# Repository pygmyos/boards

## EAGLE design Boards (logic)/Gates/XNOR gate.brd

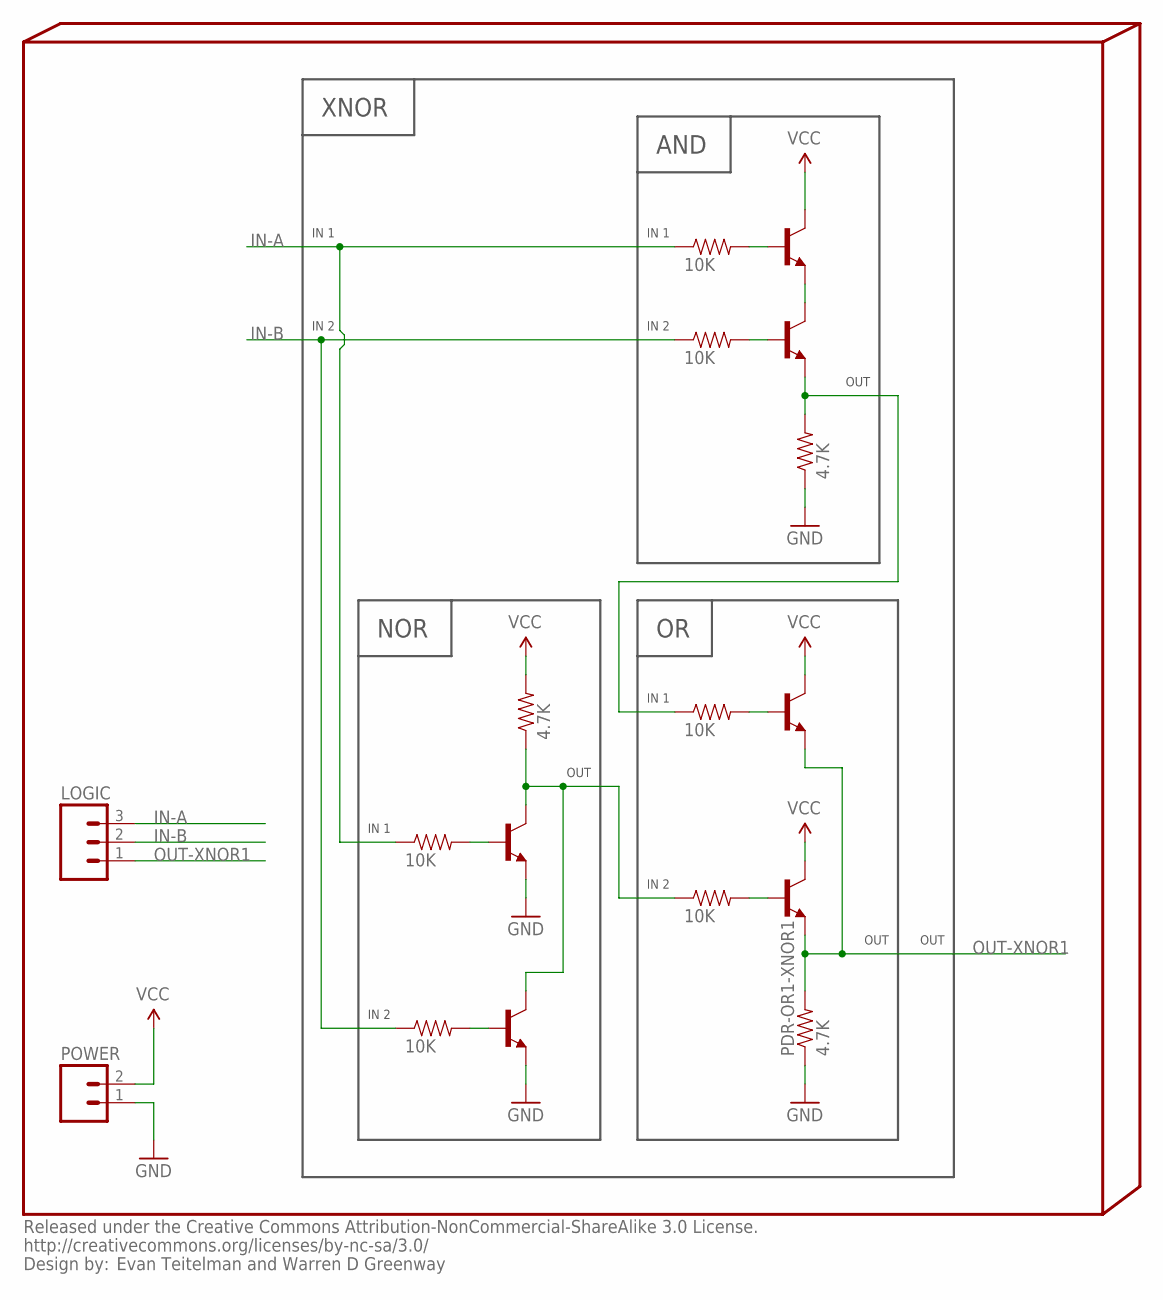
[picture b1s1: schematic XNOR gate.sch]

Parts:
INFO4: Evan Teitelman and Warren D Greenway; %CC-NC-SA
LOGIC: M03PTH; 1X03
PDR-AND1-XNOR1: 4.7K; 0402-RES
PDR-OR1-XNOR1: 4.7K; 0402-RES
POWER: M02PTH; 1X02
PUR-NOR1-XNOR1: 4.7K; 0402-RES
Q1-AND1-XNOR1, Q1-NOR1-XNOR1, Q1-OR1-XNOR1, Q2-AND1-XNOR1, Q2-NOR1-XNOR1, Q2-OR1-XNOR1: TRANSISTOR_NPNSOT23; SOT23
R1-AND1-XNOR1, R1-NOR1-XNOR1, R1-OR1-XNOR1, R2-AND1-XNOR1, R2-NOR1-XNOR1, R2-OR1-XNOR1: 10K; 0402-RES

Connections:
GND: PDR-AND1-XNOR1.1, PDR-OR1-XNOR1.1, POWER.1, Q1-NOR1-XNOR1.2 (E), Q2-NOR1-XNOR1.2 (E)
IN-A: LOGIC.3, R1-AND1-XNOR1.1, R1-NOR1-XNOR1.1
IN-B: LOGIC.2, R2-AND1-XNOR1.1, R2-NOR1-XNOR1.1
unnamed: Q1-NOR1-XNOR1.1 (B), R1-NOR1-XNOR1.2
unnamed: Q2-NOR1-XNOR1.1 (B), R2-NOR1-XNOR1.2
unnamed: Q1-AND1-XNOR1.1 (B), R1-AND1-XNOR1.2
unnamed: Q2-AND1-XNOR1.1 (B), R2-AND1-XNOR1.2
unnamed: Q2-OR1-XNOR1.1 (B), R2-OR1-XNOR1.2
unnamed: Q1-OR1-XNOR1.1 (B), R1-OR1-XNOR1.2
OUT-AND1-XNOR1: PDR-AND1-XNOR1.2, Q2-AND1-XNOR1.2 (E), R1-OR1-XNOR1.1
OUT-NOR1-XNOR1: PUR-NOR1-XNOR1.1, Q1-NOR1-XNOR1.3 (C), Q2-NOR1-XNOR1.3 (C), R2-OR1-XNOR1.1
OUT-XNOR1: LOGIC.1, PDR-OR1-XNOR1.2, Q1-OR1-XNOR1.2 (E), Q2-OR1-XNOR1.2 (E)
Q-Q-AND1-XNOR1: Q1-AND1-XNOR1.2 (E), Q2-AND1-XNOR1.3 (C)
VCC: POWER.2, PUR-NOR1-XNOR1.2, Q1-AND1-XNOR1.3 (C), Q1-OR1-XNOR1.3 (C), Q2-OR1-XNOR1.3 (C)

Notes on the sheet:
XNOR
IN 2
IN 1
OUT
AND
NOR

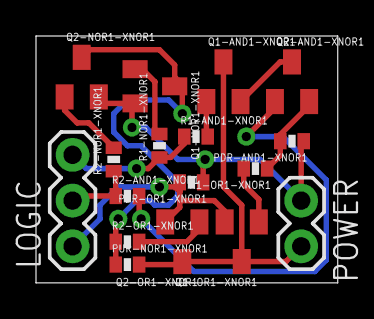
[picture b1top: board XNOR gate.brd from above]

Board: 2 copper layers, 16.8 x 13.7 mm, 18 parts (0 on the bottom side), 14 nets.

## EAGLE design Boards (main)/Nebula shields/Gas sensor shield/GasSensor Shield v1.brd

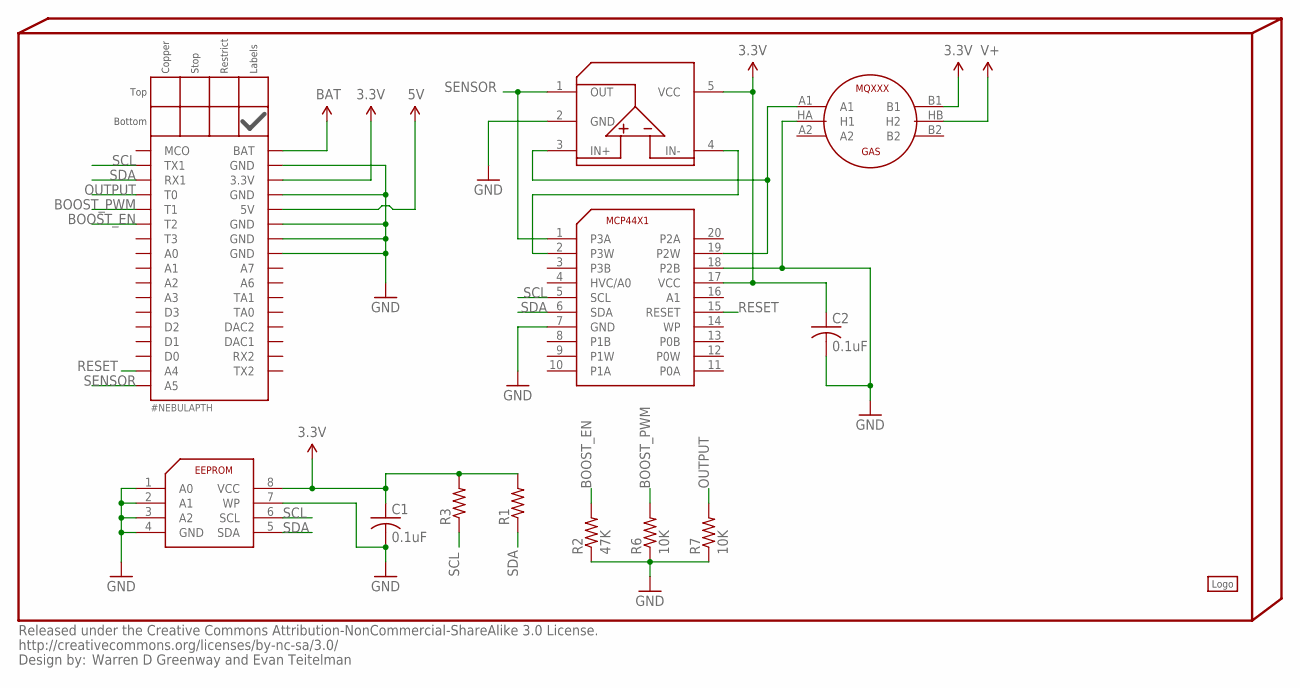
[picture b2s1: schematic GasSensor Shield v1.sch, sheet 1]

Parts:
C1, C2: 0.1uF; C0402
INFO2: Warren D Greenway and Evan Teitelman; %CC-NC-SA
LOGO1: #LOGOA-THICK
NEBULA1: #NEBULAPTH; #NEBULA-PTH
NEBULAPART1: #NEBULA-PARTLABELS-BOTTOM; #NEBULA-LABELS-BOTT
R1, R3: R-US_R0402; R0402
R2: 47K; R0402
R6, R7: 10K; R0402
U2: SENSOR-GAS-MQXXX; MQ-3
U3: EEPROM-ATMEL-AT24HC02B; TSSOP8
U4: DIGIPOT-MCP44X1; TSSOP20
U5: OPAMP-ST-LMV321RILT; SOT23-5L

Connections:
3.3V: C1.1, C2.1, NEBULA1.3.3V, R1.2, R3.2, U2.B1, U3.8 (VCC), U4.17 (VCC), U5.5 (VCC)
5V: NEBULA1.5V; also elsewhere on the board
BAT: NEBULA1.BAT; also elsewhere on the board
BOOST_EN: NEBULA1.T2, R2.2; also elsewhere on the board
BOOST_PWM: NEBULA1.T1, R6.2; also elsewhere on the board
GND: C1.2, C2.2, NEBULA1.GND1 (GND), NEBULA1.GND2 (GND), NEBULA1.GND3 (GND), NEBULA1.GND4 (GND), NEBULA1.GND5 (GND), R2.1, R6.1, R7.1, U2.HA (H1), U3.1 (A0), U3.2 (A1), U3.3 (A2), U3.4 (GND), U3.7 (WP), U4.7 (GND), U4.18 (P2B), U5.2 (GND); also elsewhere on the board
unnamed: U4.2 (P3W), U5.4 (IN-)
unnamed: U2.A1, U4.19 (P2W), U5.3 (IN+)
OUTPUT: NEBULA1.T0, R7.2; also elsewhere on the board
RESET: NEBULA1.A4, U4.15 (RESET)
SCL: NEBULA1.COM1_TX (TX1), R3.1, U3.6 (SCL), U4.5 (SCL)
SDA: NEBULA1.COM1_RX (RX1), R1.1, U3.5 (SDA), U4.6 (SDA)
SENSOR: NEBULA1.A5, U4.1 (P3A), U5.1 (OUT)
V+: U2.HB (H2); also elsewhere on the board

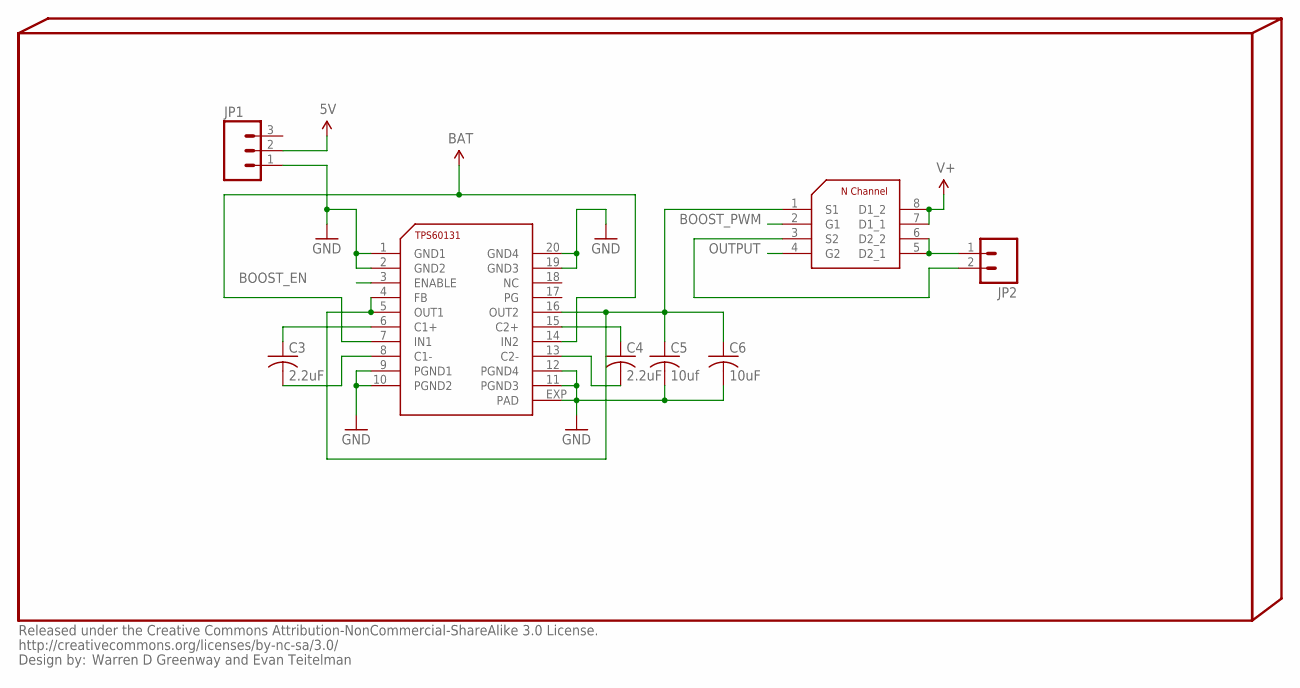
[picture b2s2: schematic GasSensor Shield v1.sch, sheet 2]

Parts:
C3, C4: 2.2uF; C0603
C5: 10uf; C0805
C6: 10uF; C0805
JP1: M03PTH; 1X03
JP2: M02PTH; 1X02
U6: REGULATOR-TI-60131; HTSSOP20PWP
U7: TRANSISTOR-VISHAY-SI7288DP; SOIC8

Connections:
5V: JP1.2; also elsewhere on the board
BAT: U6.7 (IN1), U6.14 (IN2); also elsewhere on the board
BOOST_EN: U6.3 (ENABLE); also elsewhere on the board
BOOST_PWM: U7.2 (G1); also elsewhere on the board
GND: C5.2, C6.2, JP1.1, U6.1 (GND1), U6.2 (GND2), U6.9 (PGND1), U6.10 (PGND2), U6.11 (PGND3), U6.12 (PGND4), U6.19 (GND3), U6.20 (GND4), U6.EXP (PAD); also elsewhere on the board
unnamed: C5.1, C6.1, U6.4 (FB), U6.5 (OUT1), U6.16 (OUT2), U7.1 (S1)
unnamed: C4.2, U6.13 (C2-)
unnamed: C4.1, U6.15 (C2+)
unnamed: C3.1, U6.6 (C1+)
unnamed: C3.2, U6.8 (C1-)
unnamed: JP2.1, U7.5 (D2_1), U7.6 (D2_2)
unnamed: JP2.2, U7.3 (S2)
OUTPUT: U7.4 (G2); also elsewhere on the board
V+: U7.7 (D1_1), U7.8 (D1_2); also elsewhere on the board

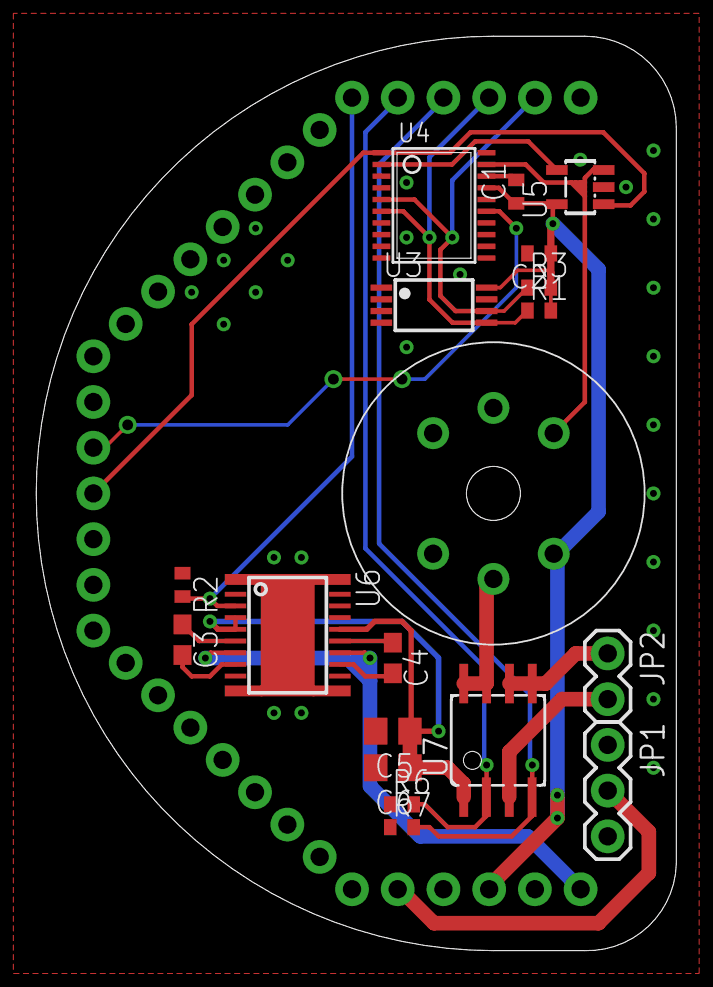
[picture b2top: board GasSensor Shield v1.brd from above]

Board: 2 copper layers, 35.6 x 50.8 mm, 23 parts (0 on the bottom side), 21 nets.

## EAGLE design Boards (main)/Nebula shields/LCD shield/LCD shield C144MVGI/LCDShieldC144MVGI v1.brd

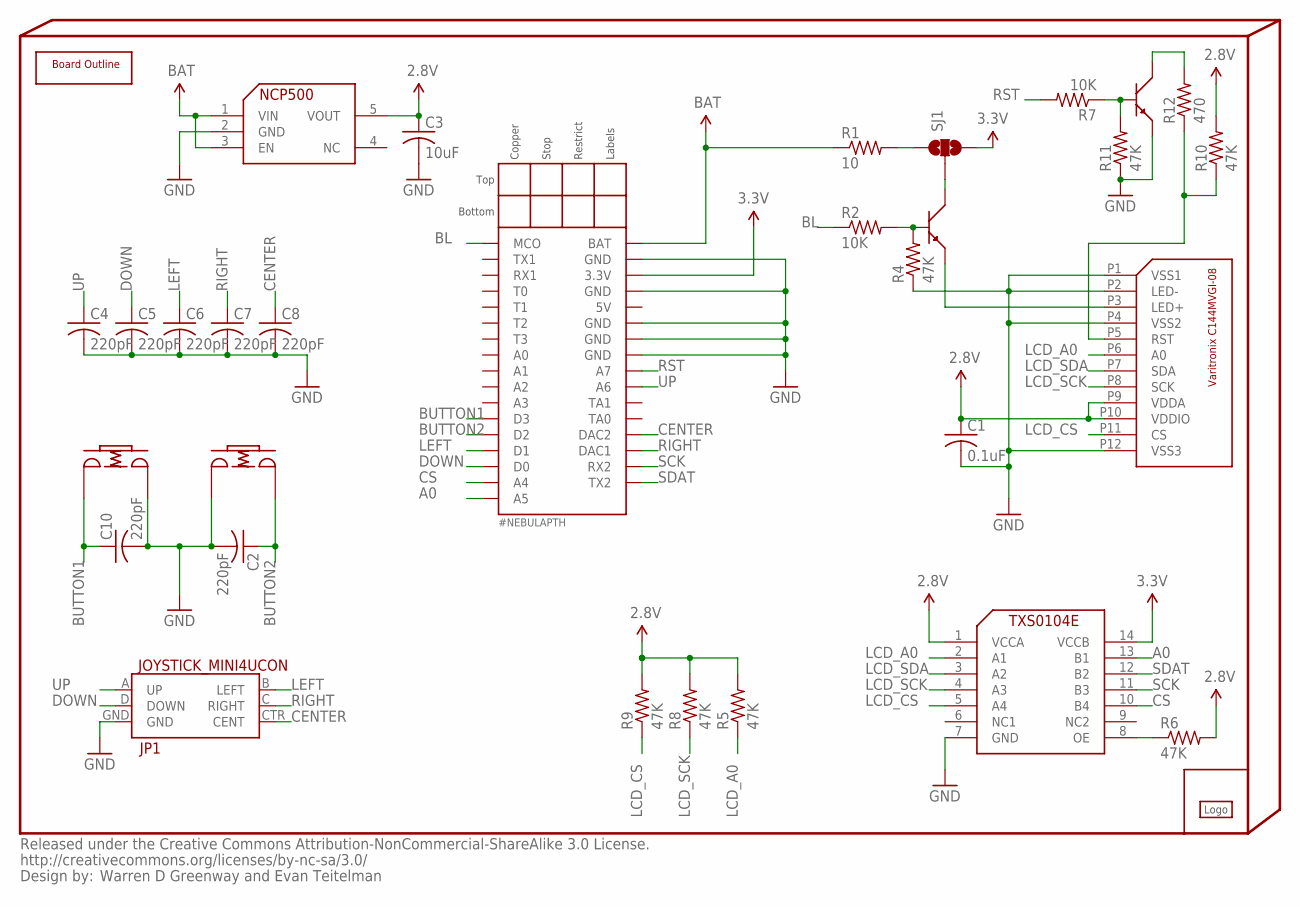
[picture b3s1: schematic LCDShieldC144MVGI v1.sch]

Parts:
BOARDOUTLINE: #NEBULA-VARITRONIX-OUTLINE
C1: 0.1uF; C0402
C2, C4, C5, C6, C7, C8, C10: 220pF; C0402
C3: 10uF; C0805
INFO3: Warren D Greenway and Evan Teitelman; %CC-NC-SA
JP1: JOYSTICK_MINI4UCON; JOYSTICK_MINI
LOGO1: #PYGMYLOGOLARGE; #PYGMYLOGO
NEBULA1: #NEBULAPTH; #NEBULA-PTH
R1: 10; R0805
R2, R7: 10K; R0402
R4, R5, R6, R8, R9, R10, R11: 47K; R0402
R12: 470; R0402
SJ1: SOLDERJUMPER_2WAYPASTE1&2; SJ_3_PASTE1&2
U1: VARITRONIX_COG-C144MVGI-08FOLDED; VARITRONIX_COG-C144MVGI-08_FOLDED
U2, U5: BIPOLAR-PMBT6428; DUBLIB_SOT23
U3: INTERFACE-TXS0104E; PW_R-PDSO-G14
U4: NCP500; SOT23-5L
U6, U7: SWITCH-ALPS-SKRG; SWITCH-2P-5MM

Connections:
2.8V: C1.1, C3.1, R5.2, R6.2, R8.2, R9.2, R10.2, U1.P9 (VDDA), U1.P10 (VDDIO), U3.1 (VCCA), U4.5 (VOUT)
3.3V: NEBULA1.3.3V, SJ1.3, U3.14 (VCCB)
A0: NEBULA1.A5, U3.13 (B1)
BAT: NEBULA1.BAT, R1.1, U4.1 (VIN), U4.3 (EN)
BL: NEBULA1.MCO, R2.1
BUTTON1: C10.1, NEBULA1.D3, U7.P1
BUTTON2: C2.1, NEBULA1.D2, U6.P2
CENTER: C8.1, JP1.CTR (CENT), NEBULA1.DAC2
CS: NEBULA1.A4, U3.10 (B4)
DOWN: C5.1, JP1.D (DOWN), NEBULA1.D0
GND: C1.2, C2.2, C3.2, C4.2, C5.2, C6.2, C7.2, C8.2, C10.2, JP1.GND, NEBULA1.GND1 (GND), NEBULA1.GND2 (GND), NEBULA1.GND3 (GND), NEBULA1.GND4 (GND), NEBULA1.GND5 (GND), R4.1, R11.1, U1.P1 (VSS1), U1.P2 (LED-), U1.P4 (VSS2), U1.P12 (VSS3), U3.7 (GND), U4.2 (GND), U5.2, U6.P1, U7.P2
LCD_A0: R5.1, U1.P6 (A0), U3.2 (A1)
LCD_CS: R9.1, U1.P11 (CS), U3.5 (A4)
LCD_SCK: R8.1, U1.P8 (SCK), U3.4 (A3)
LCD_SDA: U1.P7 (SDA), U3.3 (A2)
LEFT: C6.1, JP1.B (LEFT), NEBULA1.D1
unnamed: SJ1.2, U2.3
unnamed: R1.2, SJ1.1
unnamed: R6.1, U3.8 (OE)
unnamed: R7.1, R11.2, U5.1
unnamed: R12.2, U5.3
unnamed: U1.P3 (LED+), U2.2
unnamed: R2.2, R4.2, U2.1
unnamed: R10.1, R12.1, U1.P5 (RST)
RIGHT: C7.1, JP1.C (RIGHT), NEBULA1.DAC1
RST: NEBULA1.A7, R7.2
SCK: NEBULA1.COM2_RX (RX2), U3.11 (B3)
SDAT: NEBULA1.COM2_TX (TX2), U3.12 (B2)
UP: C4.1, JP1.A (UP), NEBULA1.A6

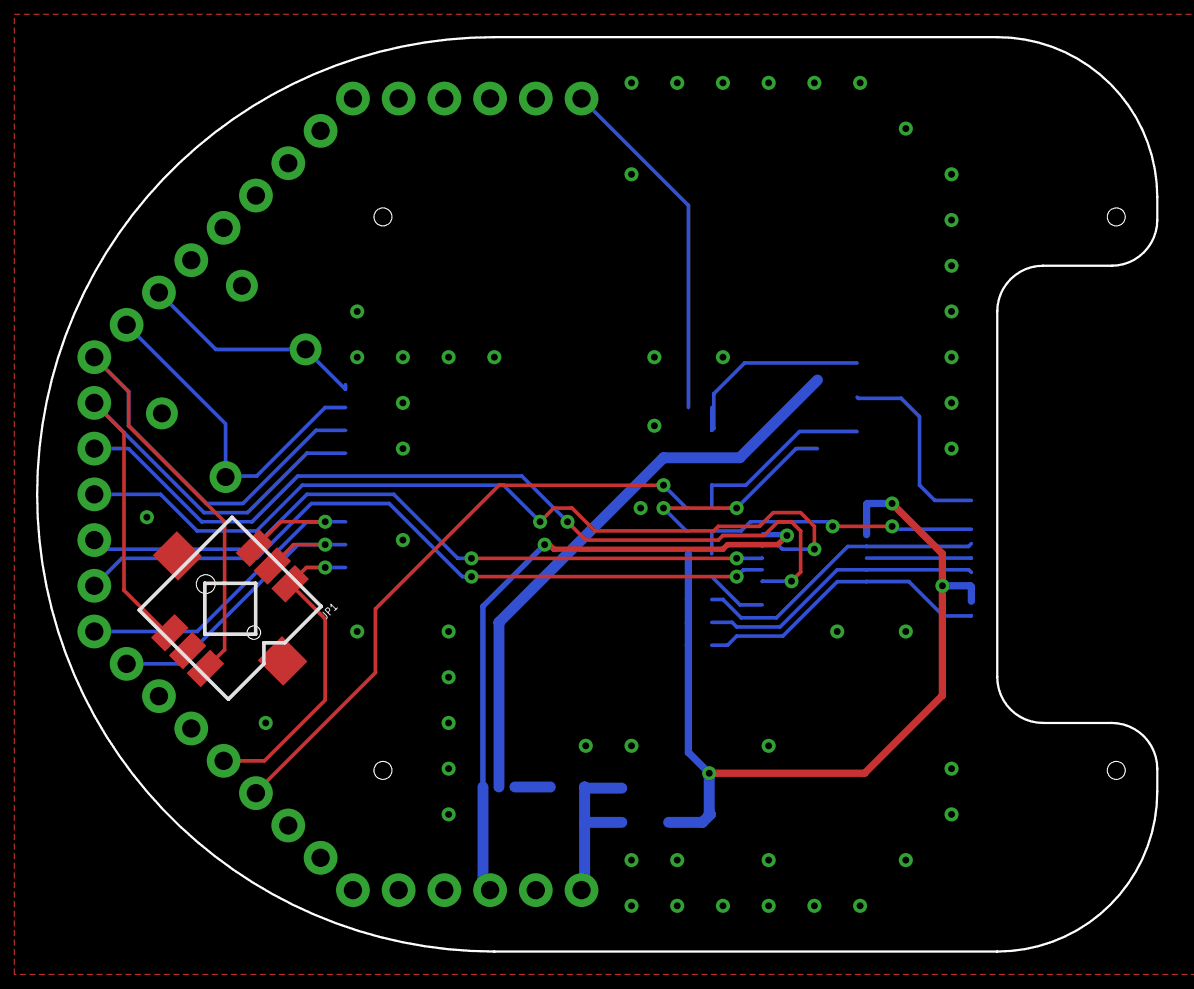
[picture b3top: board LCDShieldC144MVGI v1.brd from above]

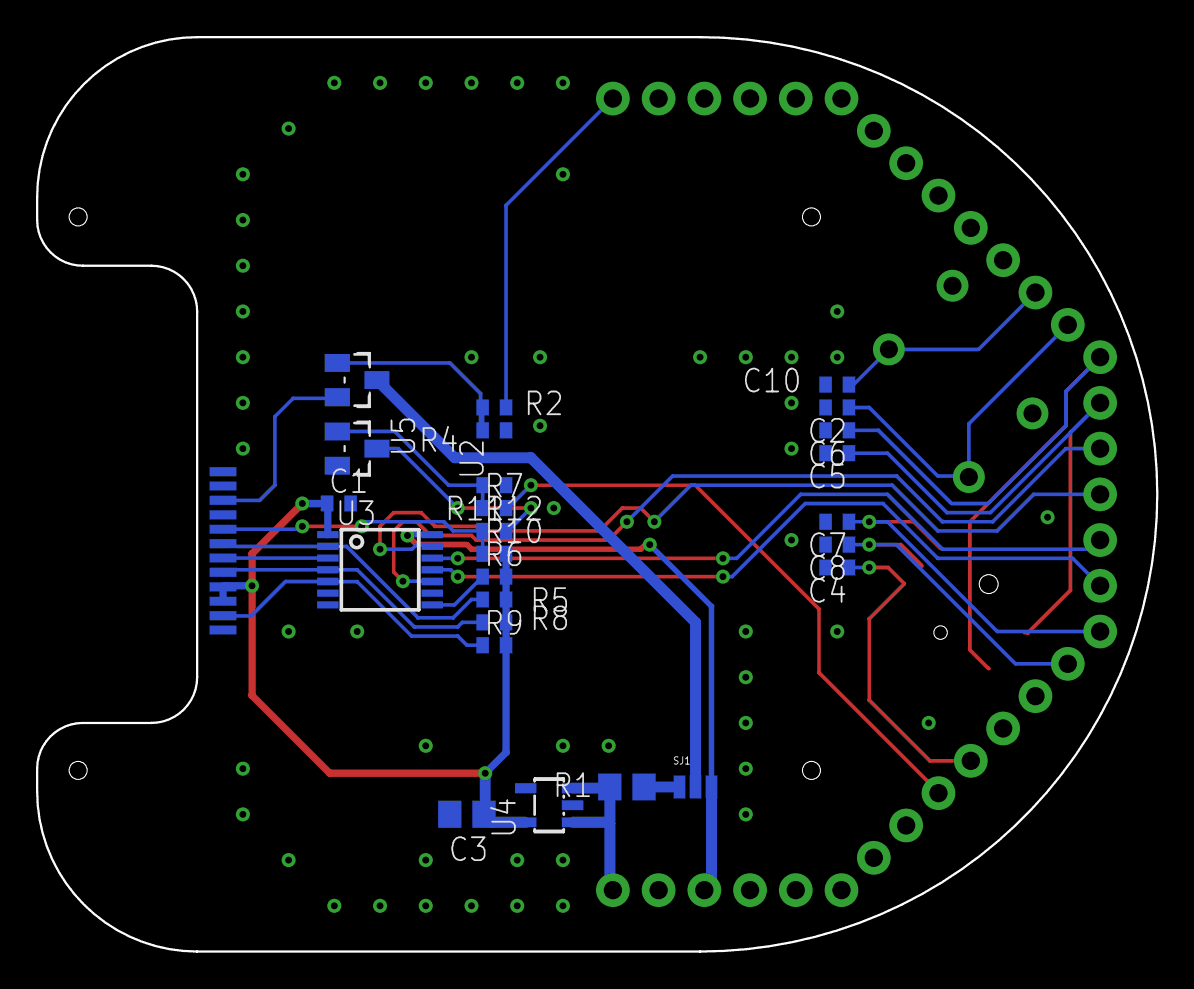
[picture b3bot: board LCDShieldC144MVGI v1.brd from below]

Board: 2 copper layers, 62.2 x 50.8 mm, 33 parts (26 on the bottom side), 29 nets.

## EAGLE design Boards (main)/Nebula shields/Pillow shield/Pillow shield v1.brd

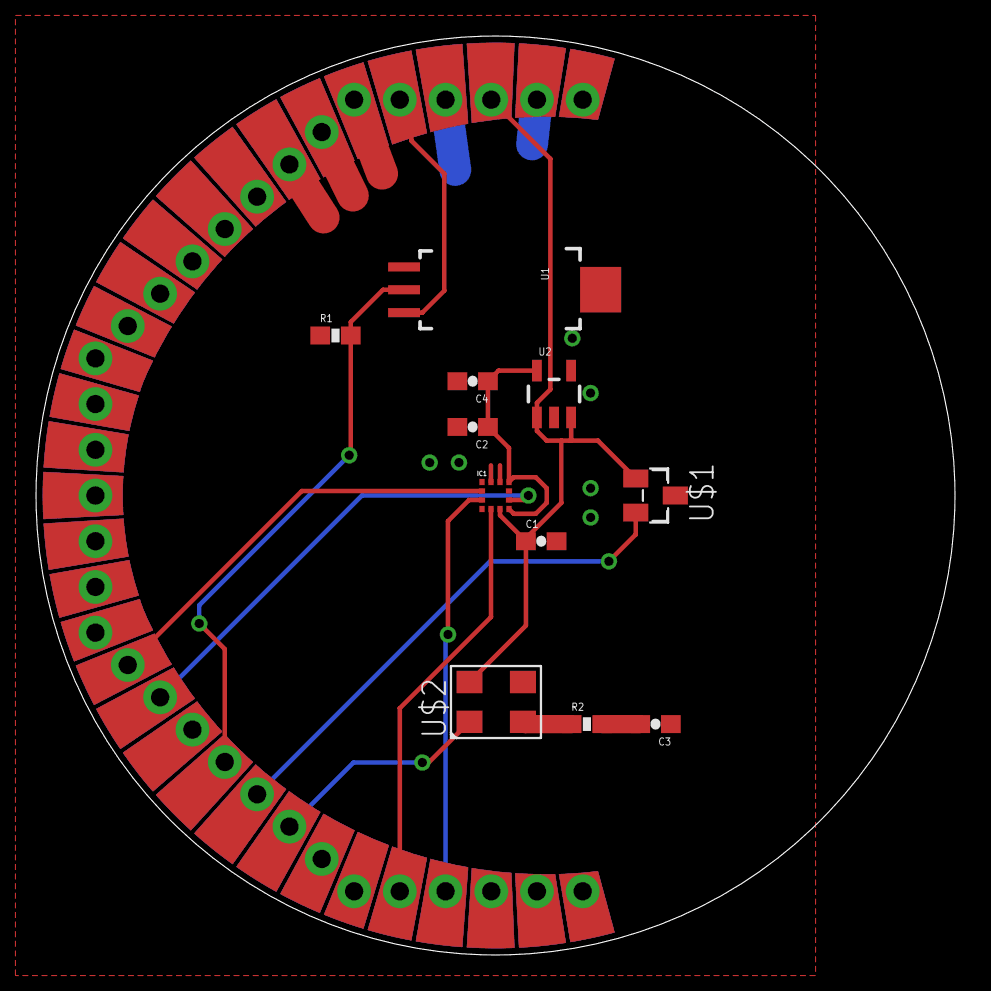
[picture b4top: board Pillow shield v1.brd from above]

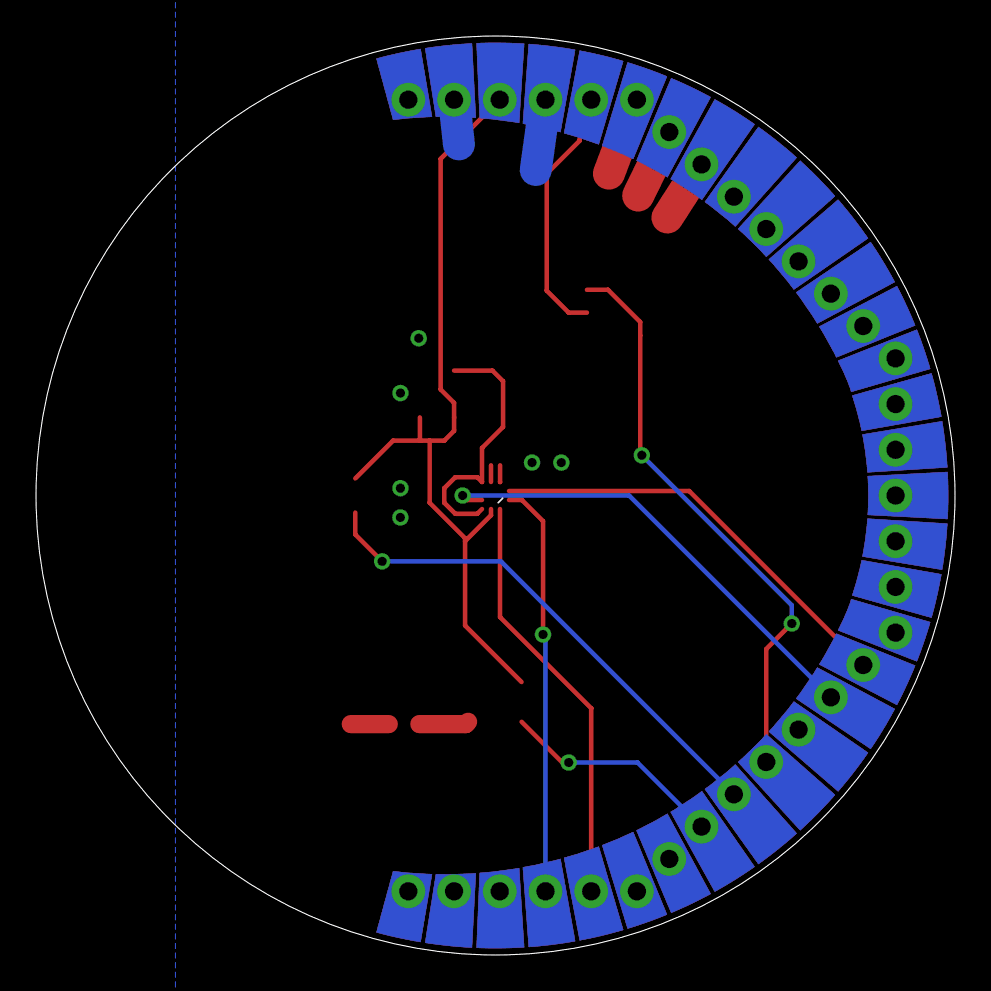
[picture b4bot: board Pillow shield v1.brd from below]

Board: 2 copper layers, 51.1 x 51.1 mm, 20 parts (5 on the bottom side), 13 nets.

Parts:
C1, C2: 100nF; 0603-CAP
C3: 0.47uF; 0603-CAP
C4: 1uF; 0603-CAP
FP1: #ETX-MAIN; #NEBULA-PTH
IC1: BMA220LGA; LGA12
INFO1: Evan Teitelman and Warren D Greenway; %CC-NC-SA
PART1, PART2: #NEBULA-PARTRESTRICT; #NEBULA-RESTRICT
PART3, PART4: #NEBULA-PARTSTOP; #NEBULA-STOP
PART5, PART6: #NEBULA-PARTPADS; #NEBULA-COPPER
PART7: #NEBULA-PARTLABELS-TOP; #NEBULA-LABELS-TOP
R1: 80K; 0603-RES
R2: 0.0; 0603-RES
U1: HIH-4030SMD; HIH-4030
U2: V_REG_LDOSMD; SOT23-5
U$1: MICROCHIP-TEMP-TC1047; SOT23
U$2: MIC_KNOWLES_SPM0408HE5H; SPM0408HE5H

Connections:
1.8V: C2.1, C4.1, IC1.4, IC1.7, U2.5
3.3V: C1.1, FP1.3.3V, IC1.3, U2.1, U2.3, U$1.1, U$2.4
5V: FP1.5V, U1.3
GAIN: R2.1, U$2.2
GND: C1.2, C2.2, C3.1, C4.2, FP1.GND1, FP1.GND2, FP1.GND3, FP1.GND4, FP1.GND5, IC1.8, IC1.9, R1.1, U1.1, U2.2, U$1.3, U$2.3
INT: FP1.D3, IC1.5
MIC: FP1.A0, U$2.1
MOIS: FP1.A2, R1.2, U1.2
unnamed: C3.2, R2.2
PS: FP1.D2, IC1.11
SCL: FP1.T0, IC1.12
SDA: FP1.T1, IC1.2
TEMP: FP1.A1, U$1.2
